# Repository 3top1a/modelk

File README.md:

<sup><sub>Render may be of an outdated version, the images below are from a CI/CD render and are always up-to-date. Only compatible with nice!nano, other MCUs won't work</sub></sup>
<div style="display: inline-flex; flex-direction: row; align-content: space-around; justify-content: space-evenly;">

</div>

Modelk is a custom replacement controller designed to add wireless Bluetooth Low Energy functionality to classic IBM Model M keyboards. This drop-in controller lets you convert your vintage buckling spring keyboard to wireless without permanent modification, preserving the original controller.

## Features

<!-- TODO Supported keyboards, M122 not tested yet -->
- Fully wireless with BLE (Bluetooth Low Energy)
- Battery powered with 3+ weeks of battery life[^batery]
- USB C for drag-and-drop programming, charging and wired use
- Compatible with IBM Model M 101/102 layouts (122-key compatibility uncertain as I do not own one yet)[^models]
- [Open source ZMK firmware](https://github.com/3top1a/modelk-zmk), with [CI/CD builds](https://github.com/3top1a/modelk-zmk/actions/workflows/build.yml)
- Works as a shield for the [nice!nano](https://nicekeyboards.com/nice-nano), built on top of the Nordic nRF52840
- All components are THT and easy to solder/repair/replace
- Three high-frequency user-configurable pins for your solenoid/speaker desires

## Hardware

### PCB

The PCB is designed in KiCad 9. This repository has a CI/CD pipeline that automatically renders the schematic into a [PDF](https://github.com/3top1a/modelk/blob/pcb-artifacts/pcb/autogen/modelk-schematic.pdf)/[SVG](https://github.com/3top1a/modelk/blob/pcb-artifacts/pcb/autogen/modelk-schematic.svg) and generates gerbers for [JLCPCB](https://github.com/3top1a/modelk/blob/pcb-artifacts/pcb/autogen/jlcpcb.zip) and [PCBWAY](https://github.com/3top1a/modelk/blob/pcb-artifacts/pcb/autogen/pcbway.zip).

### Components

See the automatically generated [iBOM](https://github.com/3top1a/modelk/blob/pcb-artifacts/pcb/autogen/ibom.html) (you will need to download the .html file and open it in your browser for now).

For a full assembly, you will need:
- 1x Modelk PCB
- 2x 74HC595 shift register ICs, preferably with DIP-16 sockets (three for M122s)
- 3x 150R resistors for the LEDs (if you have any)
- 16x 1N4148 diodes (20 for M122s)
- 1x 6x3mm reset switch ([GME](https://www.gmelectronic.com/v/1500827/kls-ts3601-43-180-microswitch) for reference)
- 1x battery and its corresponding connector (on board is JST-PH 2mm and a 2.54mm pin header for power profiling)
- PCB Faston mount ([GME](https://www.gmelectronic.com/v/1500147/dj6116-63x08-faston-do-dps-63mm) for reference)
- Appropriate [Trio-mate](https://www.te.com/en/product-6-520415-6.html) or [Connfly](https://www.tme.eu/cz/details/ds1020-16st1d/konektory-ffc-fpc-raster-2-54mm/connfly/) connectors
- 1x nice!nano with Mill Max low profile sockets

Your keyboard might contain 16+12 or 16+8+4 connectors, make sure you order the ones you need! The board supports both of them.

### Equipment

You will need:

- A Temperature-controlled soldering iron
- Some Electronics-grade solder
- Fume extraction or well-ventilated area
- A multimeter for troubleshooting
- Isopropyl alcohol for cleaning
- Kapton tape for securing the battery

### Assembly

Start with a blank PCB and solder the 16 pin connector.

On the bottom you can see the board I am assembling (revision [0.10](https://github.com/3top1a/modelk/tree/0.10)), and on the top you can see the original controller that came with my keyboard. Because I am using Connfly connectors and not the original TE Trio-mate, I need to rotate them 180° as they work differently.

> [!IMPORTANT]
> If you are using **Connfly** connectors, make sure to rotate them 180°! This sounds counter-intuitive, but **your board will not work otherwise**!

As my keyboard comes with 16+8+4 connectors, I will solder the appropriate connectors, also rotated just like the 16 pin one.

Next up are the diodes, as I have a 101-key keyboard, I will only populate the 16 left-most diodes. Pay attention to the orientation of the diodes, the black strip has to be on top, as indicated on the silkscreen.

Then the IC sockets, orientation again indicated on the silkscreen (don't forget to populate them!)

I will skip a bit here, and solder (from left to right) the Faston grounding mount, reset switch, battery connector and resistors. Just be careful soldering the Faston mount, it will get hot.

> [!CAUTION]
> Quadruple check the orientation of the battery connector! The nice!nano doesn't have reverse polarity protection and you will destroy it otherwise.

All that is left is to solder the low profile sockets, solder pins to the nice!nano (see  [official guide](https://nicekeyboards.com/docs/nice-nano/getting-started#socketing-the-nicenano)), and populate the ICs.

Here you can see the finished board (without ICs, I forgot and spent 10 minutes debugging SPI because of it), a previous iteration (revision 0.3.1) and the original controller.

Now you just need to put it into the keyboard, secure the battery with kapton tape, and mount the original grounding wire.

## Software

For now, see the [modelk-zmk](https://github.com/3top1a/modelk-zmk) repository for the ZMK firmware. Might get merged into this repository.

Installation:

- Download firmware from the modelk-zmk [CI/CD builds](https://github.com/3top1a/modelk-zmk/actions/workflows/build.yml) ([or click here for the latest firmware](https://nightly.link/3top1a/modelk-zmk/workflows/build/master/firmware.zip))
- Connect your nice!nano via USB
- Double-tap the reset button to enter bootloader mode (the little blue light should stay on)
- Your computer will detect a USB drive
- Drag and drop the firmware file (.uf2) onto this drive
- The nice!nano will disconect itself once the process is complete
- Enjoy a working wireless Model M!

By default, right alt switches to a function layer, where escape toggles USB/BT and F1-F3 toggles BT profiles, F4 clears the current BT profile, F6-F8 controls multimedia, Print Screen unlocks ZMK Studio and **Pause reboots into bootloader for updating firmware**.
You can, of course, completely redesign the layout.

## Credits

Huge kudos go to [John Hawthorn](https://www.johnhawthorn.com/) for his [Model H](https://modelh.club/) controller that inspired this project. This repo started as a fork, but now doesn't share any files.

[^batery]: currently ~3 weeks on a 400mAh battery with revision 0.3.1, will be better on newer boards

[^models]: Tested on: 1386716

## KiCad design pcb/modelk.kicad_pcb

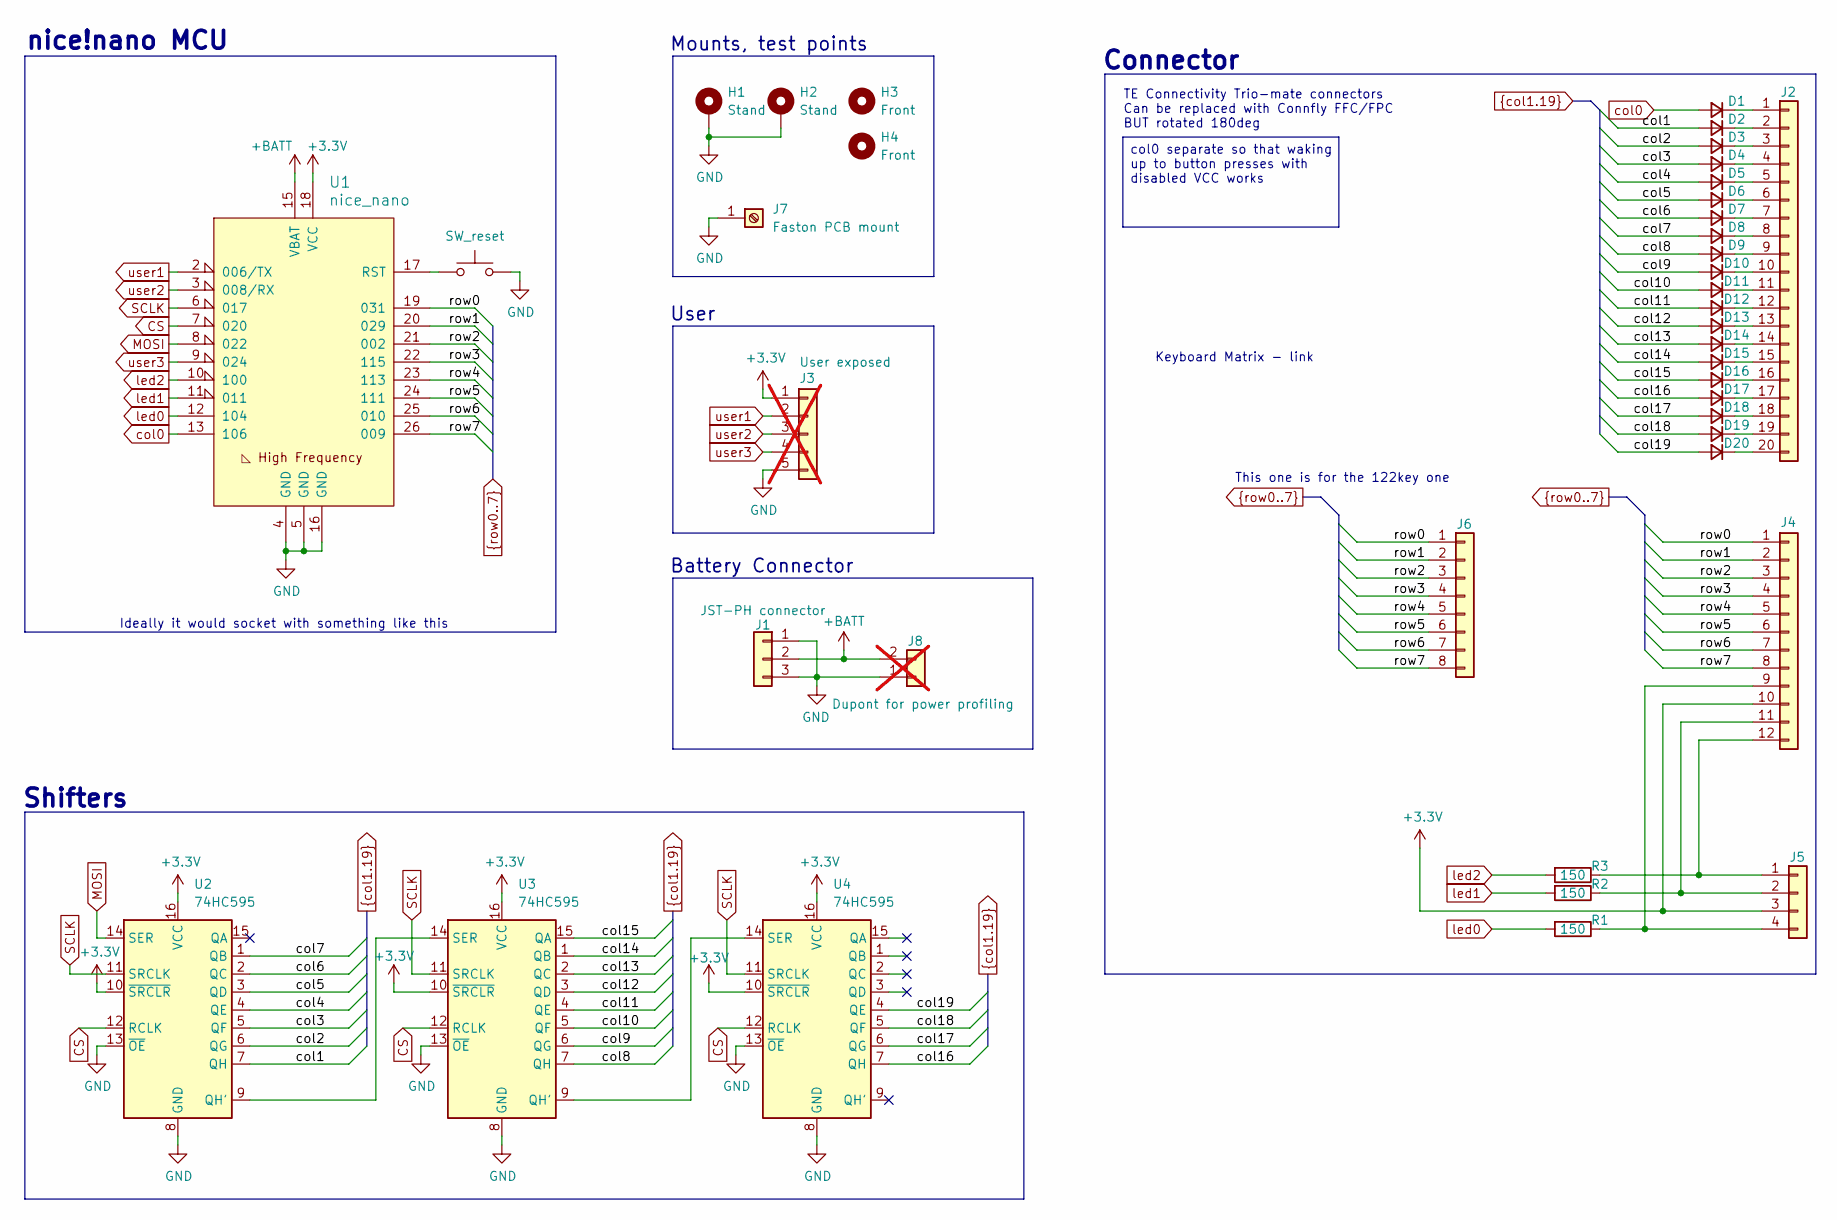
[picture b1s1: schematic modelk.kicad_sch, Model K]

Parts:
D1, D2, D3, D4, D5, D6, D7, D8, D9, D10, D11, D12, D13, D14, D15, D16, D17, D18, D19, D20: D_Small; DO-35 smaller
H1, H2: Stand; MountingHole_4mm_Pad_Via
H3, H4: Front; Hole 3.5mm
J1: JST-PH connector; JST_PH_B3B-PH-K_1x03_P2.00mm_Vertical
J2: Conn_01x20; ffc-cols20
J3: User exposed; PinHeader_1x05_P2.54mm_Vertical; not fitted
J4: Conn_01x12; ffc-rows12
J5: Conn_01x04; ffc-leds4
J6: Conn_01x08; ffc-rows8
J7: Faston PCB mount; faston-mount
J8: Dupont for power profiling; BatteryHeader; not fitted
R1, R2, R3: 150; R_Axial_DIN0207_L6.3mm_D2.5mm_P10.16mm_Horizontal
SW1: SW_reset; SW_PUSH_1P1T_6x3.5mm_H4.3_APEM_MJTP1243
U1: nice_nano
U2, U3, U4: 74HC595; DIP-16-74HC595

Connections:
+3.3V: J3.1, J4.10, J5.3, U1.18 (VCC), U2.10 (~SRCLR), U2.16 (VCC), U3.10 (~SRCLR), U3.16 (VCC), U4.10 (~SRCLR), U4.16 (VCC)
+BATT: J1.2, J8.2, U1.15 (VBAT)
/col1: D2.2 (A), U2.7 (QH)
/col2: D3.2 (A), U2.6 (QG)
/col3: D4.2 (A), U2.5 (QF)
/col4: D5.2 (A), U2.4 (QE)
/col5: D6.2 (A), U2.3 (QD)
/col6: D7.2 (A), U2.2 (QC)
/col7: D8.2 (A), U2.1 (QB)
/col8: D9.2 (A), U3.7 (QH)
/col9: D10.2 (A), U3.6 (QG)
/col10: D11.2 (A), U3.5 (QF)
/col11: D12.2 (A), U3.4 (QE)
/col12: D13.2 (A), U3.3 (QD)
/col13: D14.2 (A), U3.2 (QC)
/col14: D15.2 (A), U3.1 (QB)
/col15: D16.2 (A), U3.15 (QA)
/col16: D17.2 (A), U4.7 (QH)
/col17: D18.2 (A), U4.6 (QG)
/col18: D19.2 (A), U4.5 (QF)
/col19: D20.2 (A), U4.4 (QE)
/row0: J4.1, J6.1, U1.19 (031)
/row1: J4.2, J6.2, U1.20 (029)
/row2: J4.3, J6.3, U1.21 (002)
/row3: J4.4, J6.4, U1.22 (115)
/row4: J4.5, J6.5, U1.23 (113)
/row5: J4.6, J6.6, U1.24 (111)
/row6: J4.7, J6.7, U1.25 (010)
/row7: J4.8, J6.8, U1.26 (009)
CS: U1.7 (020), U2.12 (RCLK), U3.12 (RCLK), U4.12 (RCLK)
GND: H1.1, H2.1, J1.1, J1.3, J3.5, J7.1, J8.1, SW1.1, U1.4 (GND), U1.5 (GND), U1.16 (GND), U2.8 (GND), U2.13 (~OE), U3.8 (GND), U3.13 (~OE), U4.8 (GND), U4.13 (~OE)
MOSI: U1.8 (022), U2.14 (SER)
unnamed: D1.1 (K), J2.1
unnamed: D2.1 (K), J2.2
unnamed: D3.1 (K), J2.3
unnamed: D4.1 (K), J2.4
unnamed: D5.1 (K), J2.5
unnamed: D6.1 (K), J2.6
unnamed: D7.1 (K), J2.7
unnamed: D8.1 (K), J2.8
unnamed: D9.1 (K), J2.9
unnamed: D10.1 (K), J2.10
unnamed: D11.1 (K), J2.11
unnamed: D12.1 (K), J2.12
unnamed: D13.1 (K), J2.13
unnamed: D14.1 (K), J2.14
unnamed: D15.1 (K), J2.15
unnamed: D16.1 (K), J2.16
unnamed: D17.1 (K), J2.17
unnamed: D18.1 (K), J2.18
unnamed: D19.1 (K), J2.19
unnamed: D20.1 (K), J2.20
unnamed: J4.9, J5.4, R1.1
unnamed: J4.11, J5.2, R2.1
unnamed: J4.12, J5.1, R3.1
unnamed: SW1.2, U1.17 (RST)
unnamed: U2.9 (QH'), U3.14 (SER)
unnamed: U3.9 (QH'), U4.14 (SER)
SCLK: U1.6 (017), U2.11 (SRCLK), U3.11 (SRCLK), U4.11 (SRCLK)
col0: D1.2 (A), U1.13 (106)
led0: R1.2, U1.12 (104)
led1: R2.2, U1.11
led2: R3.2, U1.10 (100)
user1: J3.2, U1.2 (006/TX)
user2: J3.3, U1.3 (008/RX)
user3: J3.4, U1.9 (024)

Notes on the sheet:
Ideally it would socket with something like this
Shifters
User
Keyboard Matrix - link
Mounts, test points
TE Connectivity Trio-mate connectors Can be replaced with Connfly FFC/FPC BUT rotated 180deg
Connector
Battery Connector
nice!nano MCU
This one is for the 122key one
col0 separate so that waking up to button presses with disabled VCC works

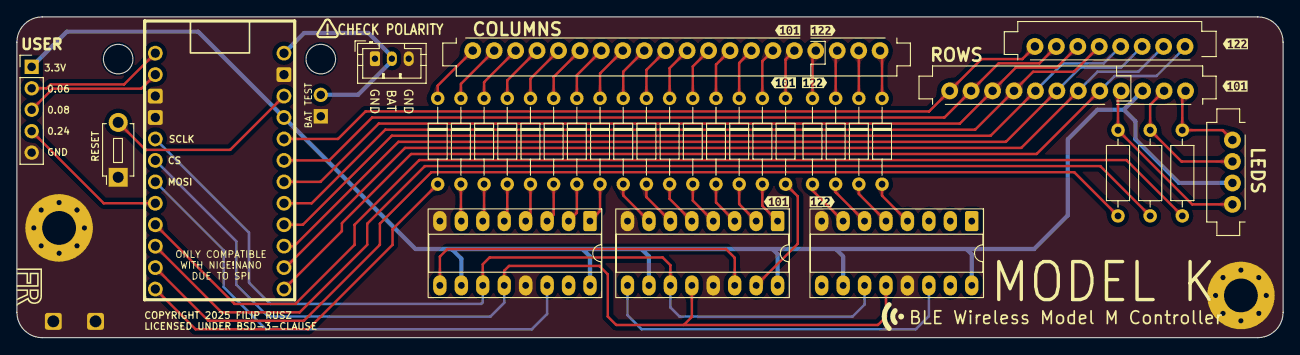
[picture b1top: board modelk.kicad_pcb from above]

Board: 2 copper layers, 150.0 x 38.0 mm, 48 parts (0 on the bottom side), 66 nets.

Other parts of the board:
kibuzzard-684FF5A3: G***; kibuzzard-684FF5A3
kibuzzard-684FF45F, kibuzzard-684FF45F#2, kibuzzard-684FF45F#3, kibuzzard-684FF45F#4: G***; kibuzzard-684FF45F
kibuzzard-684FF466, kibuzzard-684FF466#2, kibuzzard-684FF466#3: G***; kibuzzard-684FF466

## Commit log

2025-03-01 v0.1
2025-04-30 version 0.2
2025-04-30 Added license
2025-05-12 Rev 0.3
2025-05-12 Small edits
2025-05-12 Make it compatable with old pro micro
2025-05-13 v3.1; made it uncompatible because HF pins
2025-05-20 Added actual reset switch
2025-06-04 Aligned connectors correctly, added second 4 pin footprint
2025-06-04 Added testpad labels, ibom
2025-06-04 Added third hole for M122
2025-06-04 101 key was correct
2025-06-04 Mostly stylistic changes
2025-06-11 Better models, added SGA font, col0 separate
2025-06-14 v0.7, too much to comment
2025-06-14 updated ibom
2025-06-14 Rename files
2025-06-14 Shim is now outdated
2025-06-15 Added faston ground connector
2025-06-15 Fixed DRC
2025-06-15 Added blender render
2025-06-15 Move traces so ground pour is continuous
2025-06-15 Move stuff
2025-06-15 Added battery header for profiling
2025-06-15 Removed mount holes from ffc connectors
    This also fixes all DRC errors.
2025-06-15 Actions test
2025-06-15 artifacts in another branch
2025-06-15 force push to artifacts
2025-06-15 Update PCB artifacts from KiBot
2025-06-15 All leds on high frequency pins
2025-06-17 Remade half the board
    Redid the visual language, standardized the font and its size.
    Moved diodes closer to connector.
    Text is all caps now.
2025-06-17 Better font
2025-06-17 Unforce push in kibot.yml
2025-06-17 Fix CI?
2025-06-17 Embeded SGA font
2025-06-17 Modified user text to be the actual pin
2025-06-18 Labels
2025-06-18 Also render to png
2025-06-18 Added pictograms
2025-06-18 Updated splash
2025-06-18 Fixed connector position
    Also added Designed In CZ text on silkscreen and distributed traces in
    the middle.
2025-06-18 Basic readme
2025-06-18 Deleted everything other than autogen
2025-06-18 Don't put logos into the iBOM
2025-06-18 Don't put logos into the iBOM x2
2025-06-18 More readme
2025-06-18 Made silkscreen not intersect
2025-06-19 Updated calculation
2025-06-19 Spaced out signal tracks, less vias
2025-06-19 One less via
2025-06-19 Spaced out traces, zero vias!
2025-06-19 Fixed silkscreen
2025-06-19 Updated sclk/cs silkscreen
2025-06-26 Credit John for the original repo
2025-07-20 Added pause reboots to readme
2025-07-20 Spelling
2025-10-24 Fix 'Model K' to 'Modelk'

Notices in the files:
pcb/modelk.kicad_pcb:
COPYRIGHT 2025 FILIP RUSZ
LICENSED UNDER BSD-3-CLAUSE
